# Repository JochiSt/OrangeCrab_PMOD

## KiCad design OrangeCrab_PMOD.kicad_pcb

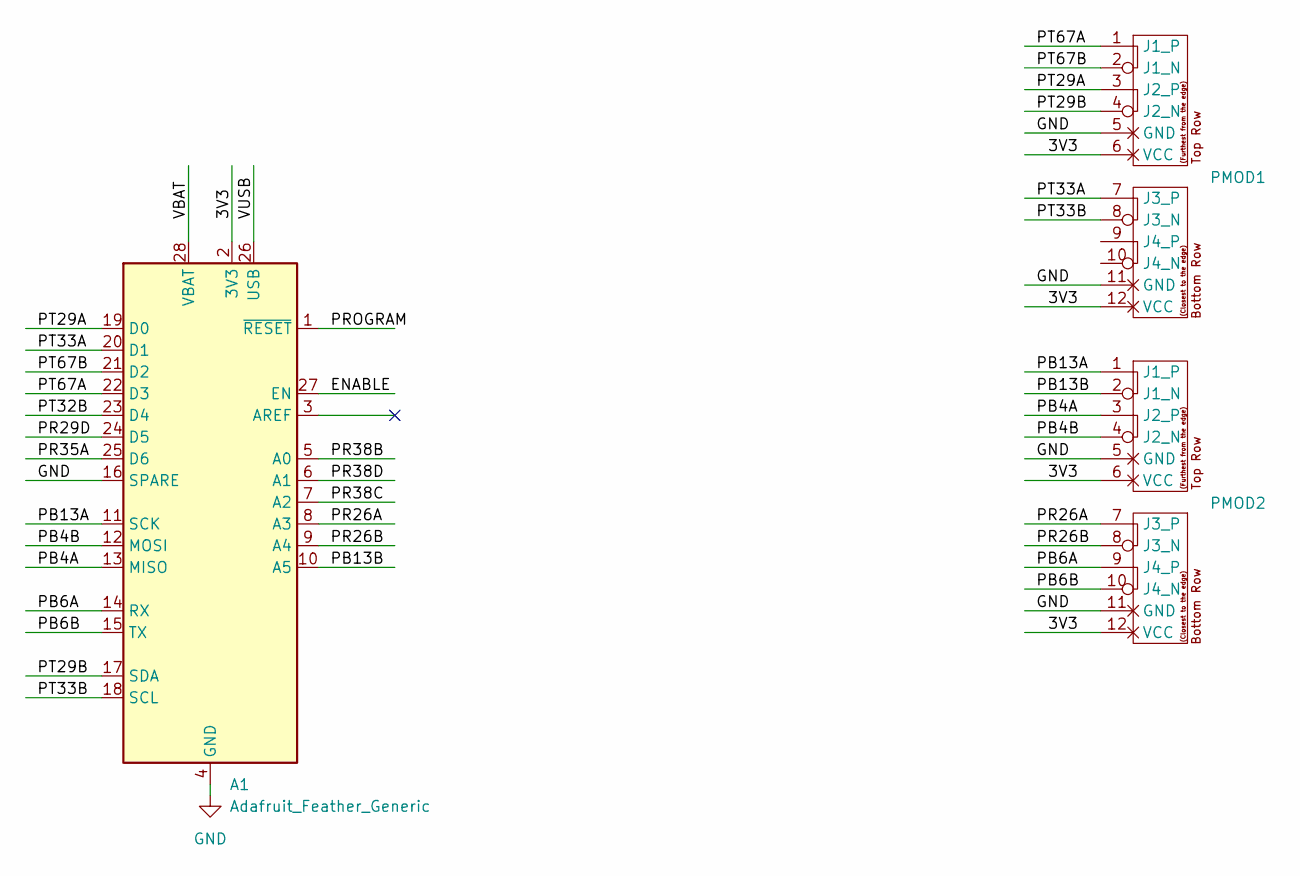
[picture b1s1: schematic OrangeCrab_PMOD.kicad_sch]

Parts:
A1: Adafruit_Feather_Generic; Adafruit_Feather
PMOD1, PMOD2: PMOD-Device-x2-Type-XHS; pmod_pin_array_6x2

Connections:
/3V3: A1.2 (3V3), PMOD1.6 (VCC), PMOD1.12 (VCC), PMOD2.6 (VCC), PMOD2.12 (VCC)
/ENABLE: A1.27 (EN)
/PB4A: A1.13 (MISO), PMOD2.3 (J2_P)
/PB4B: A1.12 (MOSI), PMOD2.4 (J2_N)
/PB6A: A1.14 (RX), PMOD2.9 (J4_P)
/PB6B: A1.15 (TX), PMOD2.10 (J4_N)
/PB13A: A1.11 (SCK), PMOD2.1 (J1_P)
/PB13B: A1.10 (A5), PMOD2.2 (J1_N)
/PR26A: A1.8 (A3), PMOD2.7 (J3_P)
/PR26B: A1.9 (A4), PMOD2.8 (J3_N)
/PR29D: A1.24 (D5)
/PR35A: A1.25 (D6)
/PR38B: A1.5 (A0)
/PR38C: A1.7 (A2)
/PR38D: A1.6 (A1)
/PROGRAM: A1.1 (~RESET)
/PT29A: A1.19 (D0), PMOD1.3 (J2_P)
/PT29B: A1.17 (SDA), PMOD1.4 (J2_N)
/PT32B: A1.23 (D4)
/PT33A: A1.20 (D1), PMOD1.7 (J3_P)
/PT33B: A1.18 (SCL), PMOD1.8 (J3_N)
/PT67A: A1.22 (D3), PMOD1.1 (J1_P)
/PT67B: A1.21 (D2), PMOD1.2 (J1_N)
/VBAT: A1.28 (VBAT)
/VUSB: A1.26 (USB)
GND: A1.4 (GND), A1.16 (SPARE), PMOD1.5 (GND), PMOD1.11 (GND), PMOD2.5 (GND), PMOD2.11 (GND)

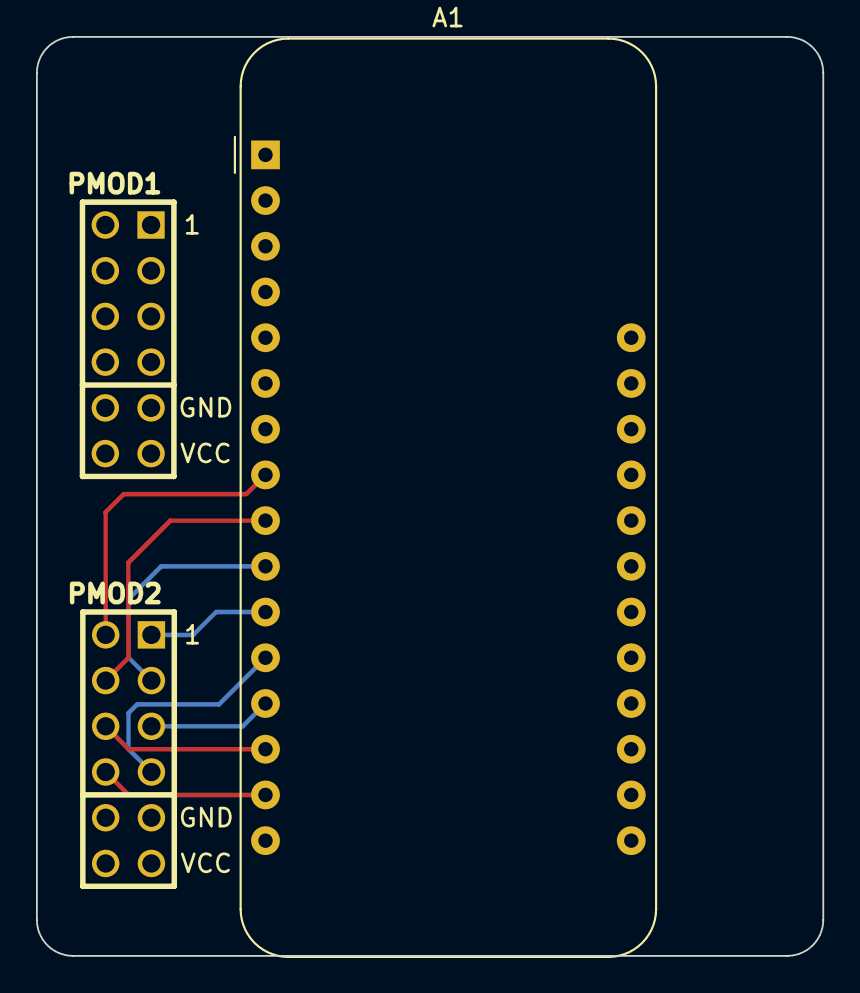
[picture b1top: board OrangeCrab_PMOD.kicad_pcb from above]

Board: 2 copper layers, 43.7 x 51.1 mm, 3 parts (0 on the bottom side), 16 nets.

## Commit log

2023-09-21 added Feather Connectors and labelled the signals according to the orange crab
2023-10-08 added submodule for feather board layout
2023-10-08 started layout and connectors to Orange Crab
2023-10-08 ignore lck files
2025-03-06 updated to KiCAD v9
2025-03-06 added fillet of 2mm to board outline
